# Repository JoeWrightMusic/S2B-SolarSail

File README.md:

# S2B-SolarSail
'Solar Sail' interactive object for Oily Cart's 'Space to Be' (2023)

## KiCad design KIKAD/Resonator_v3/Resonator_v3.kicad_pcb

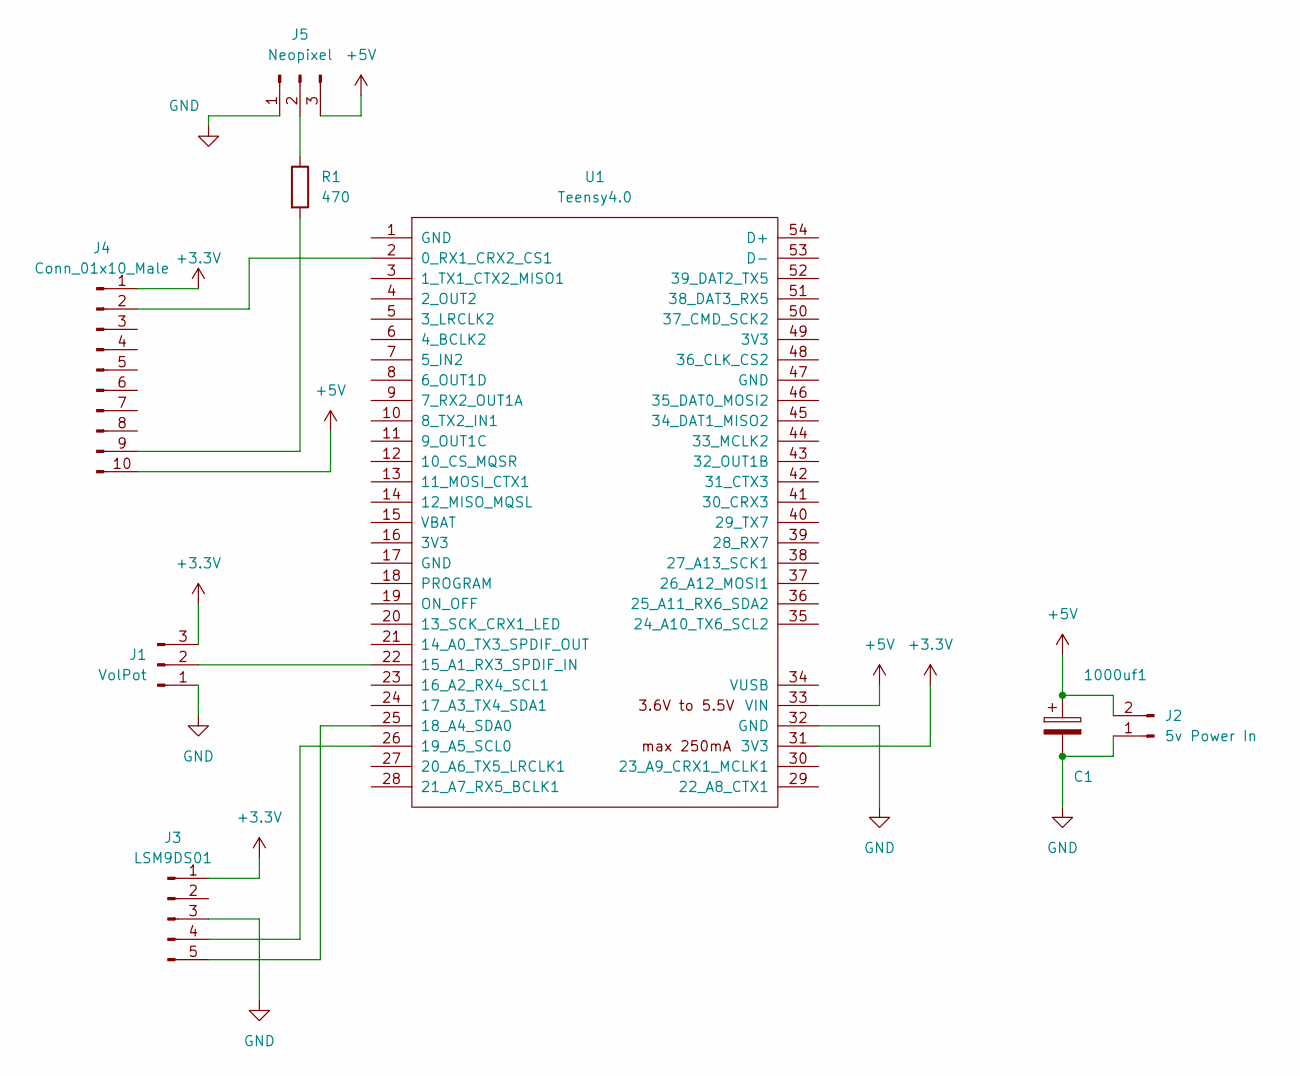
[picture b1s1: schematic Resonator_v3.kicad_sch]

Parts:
1000uf1: C1; CP_Radial_D10.0mm_P7.50mm
J1: VolPot; Molex_KK-254_AE-6410-03A_1x03_P2.54mm_Vertical
J2: 5v Power In; Molex_KK-254_AE-6410-02A_1x02_P2.54mm_Vertical
J3: LSM9DS01; Molex_KK-254_AE-6410-05A_1x05_P2.54mm_Vertical
J4: Conn_01x10_Male; SW_DIP_SPSTx05_Piano_10.8x14.26mm_W7.62mm_P2.54mm
J5: Neopixel; Molex_KK-254_AE-6410-03A_1x03_P2.54mm_Vertical
R1: 470; R_Axial_DIN0204_L3.6mm_D1.6mm_P7.62mm_Horizontal
U1: Teensy4.0; Teensy40

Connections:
+3V3: J1.3, J3.1, J4.1, U1.31 (3V3)
+5V: 1000uf1.1, J2.2, J4.10, J5.3, U1.33 (VIN)
GND: 1000uf1.2, J1.1, J2.1, J3.3, J5.1, U1.32 (GND)
unnamed: J1.2, U1.22 (15_A1_RX3_SPDIF_IN)
unnamed: J4.2, U1.2 (0_RX1_CRX2_CS1)
unnamed: J4.9, R1.2
unnamed: J5.2, R1.1
unnamed: J3.5, U1.25 (18_A4_SDA0)
unnamed: J3.4, U1.26 (19_A5_SCL0)

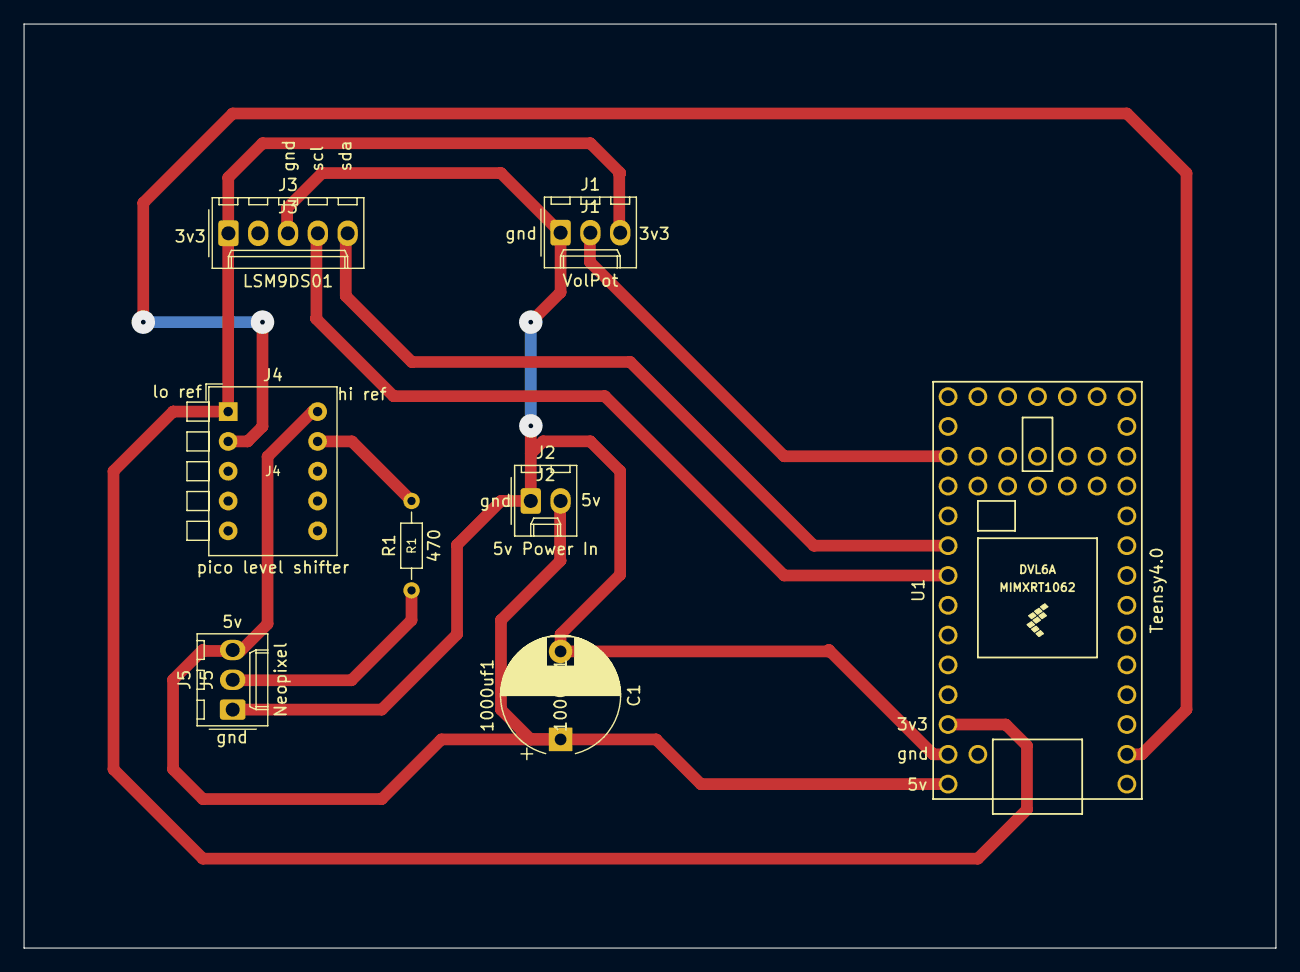
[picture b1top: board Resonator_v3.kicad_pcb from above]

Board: 2 copper layers, 106.7 x 78.7 mm, 8 parts (0 on the bottom side), 9 nets.

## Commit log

2023-02-28 First commit - collecting project files in one place
2023-03-01 audio and teensy sketch updated
2023-05-09 Audio Files Added
